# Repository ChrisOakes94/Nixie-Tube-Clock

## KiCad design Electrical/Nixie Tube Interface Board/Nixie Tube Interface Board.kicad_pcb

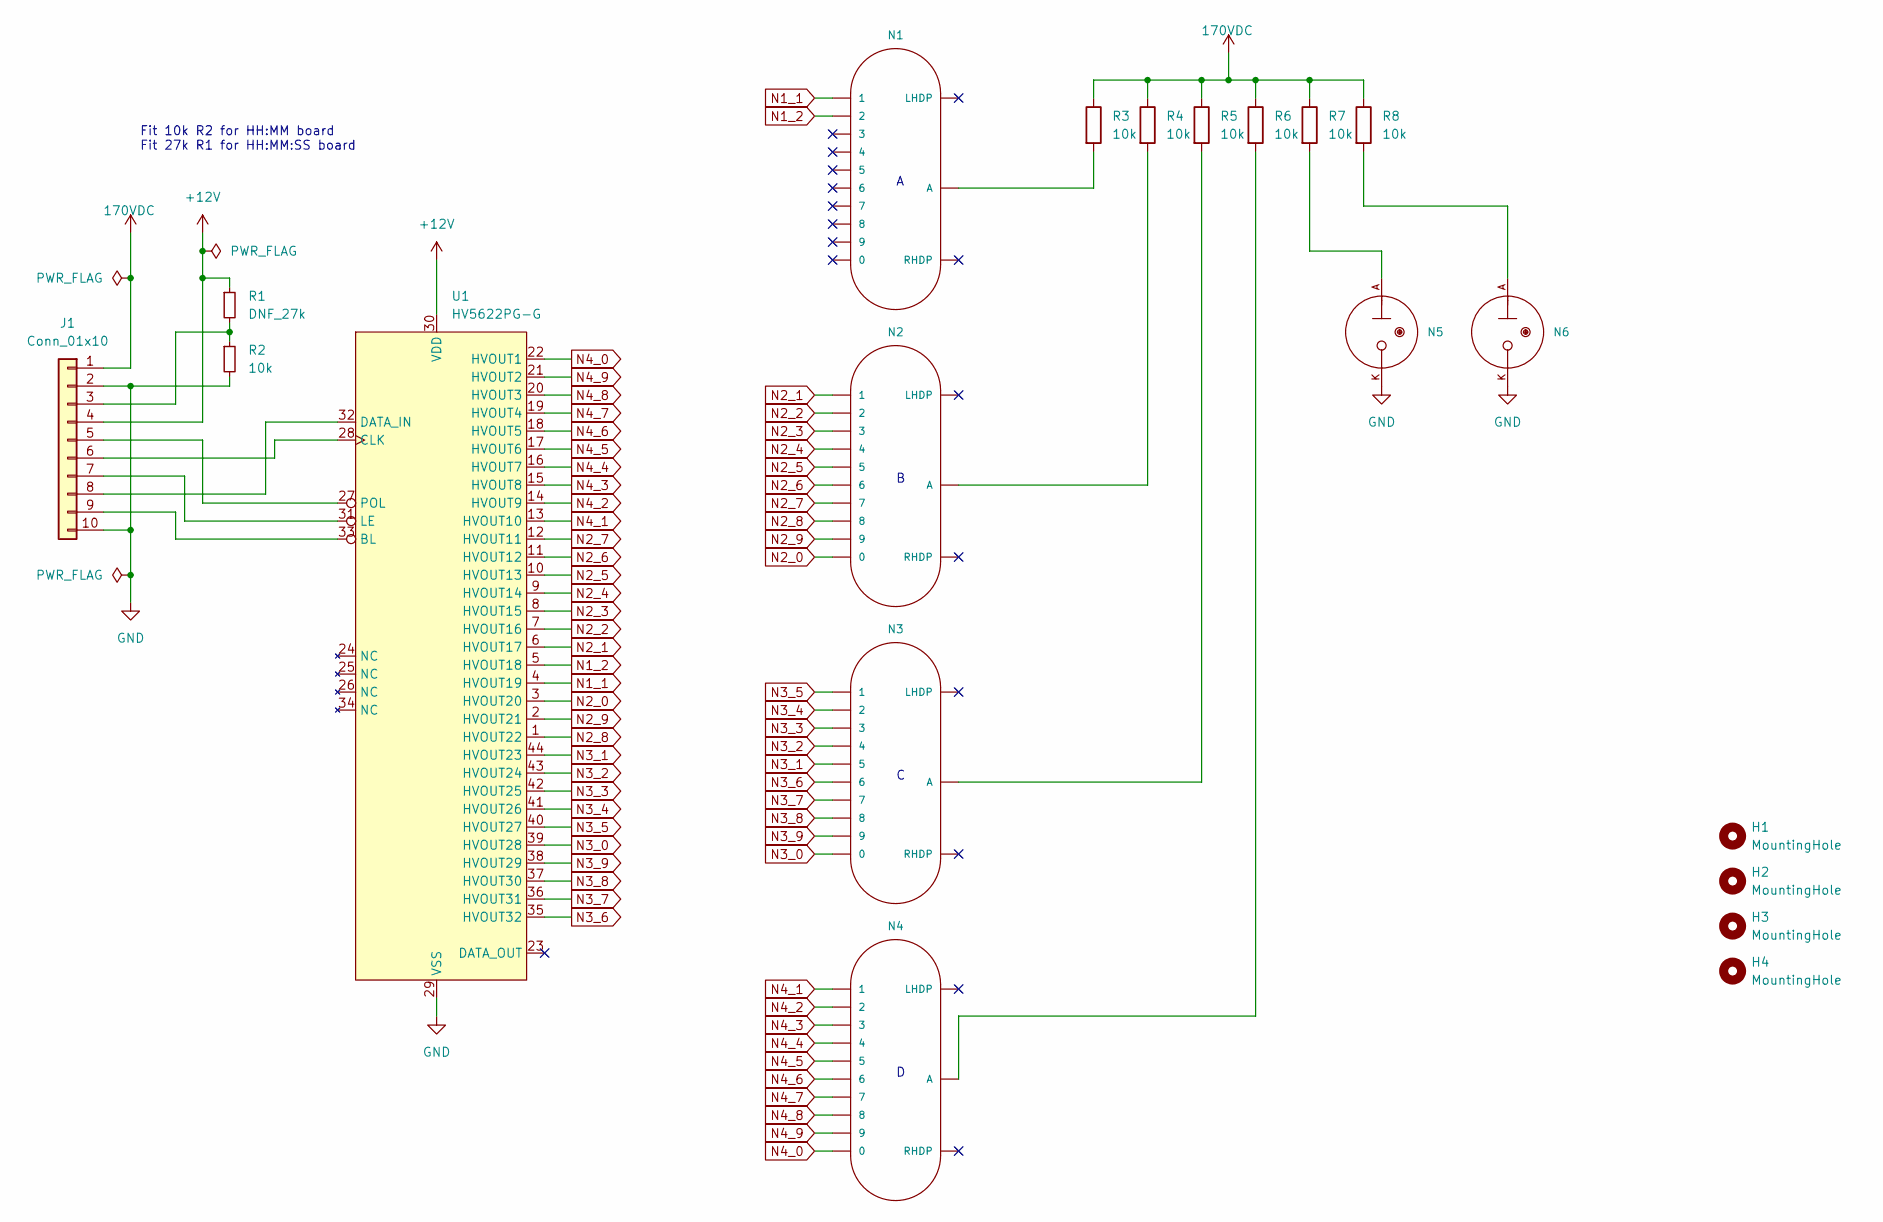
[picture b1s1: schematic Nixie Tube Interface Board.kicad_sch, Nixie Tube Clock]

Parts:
H1, H2, H3, H4: MountingHole; MountingHole_3.2mm_M3
J1: Conn_01x10; PinSocket_1x10_P2.54mm_Vertical
N1, N2, N3, N4: IN-14; nixies-us-IN-14
N5, N6: IN-3; nixies-us-IN-3
R1: DNF_27k; R_1206_3216Metric_Pad1.30x1.75mm_HandSolder
R2, R3, R4, R5, R6, R7, R8: 10k; R_1206_3216Metric_Pad1.30x1.75mm_HandSolder
U1: HV5622PG-G; LQFP-44_10x10mm_P0.8mm

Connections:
+12V: J1.4, R1.1, U1.30 (VDD)
+170VDC: J1.1, R3.1, R4.1, R5.1, R6.1, R7.1, R8.1
GND: J1.2, J1.10, N5.K, N6.K, R2.2, U1.29 (VSS)
N1_1: N1.1, U1.4 (HVOUT19)
N1_2: N1.2, U1.5 (HVOUT18)
N2_0: N2.0, U1.3 (HVOUT20)
N2_1: N2.1, U1.6 (HVOUT17)
N2_2: N2.2, U1.7 (HVOUT16)
N2_3: N2.3, U1.8 (HVOUT15)
N2_4: N2.4, U1.9 (HVOUT14)
N2_5: N2.5, U1.10 (HVOUT13)
N2_6: N2.6, U1.11 (HVOUT12)
N2_7: N2.7, U1.12 (HVOUT11)
N2_8: N2.8, U1.1 (HVOUT22)
N2_9: N2.9, U1.2 (HVOUT21)
N3_0: N3.0, U1.39 (HVOUT28)
N3_1: N3.5, U1.44 (HVOUT23)
N3_2: N3.4, U1.43 (HVOUT24)
N3_3: N3.3, U1.42 (HVOUT25)
N3_4: N3.2, U1.41 (HVOUT26)
N3_5: N3.1, U1.40 (HVOUT27)
N3_6: N3.6, U1.35 (HVOUT32)
N3_7: N3.7, U1.36 (HVOUT31)
N3_8: N3.8, U1.37 (HVOUT30)
N3_9: N3.9, U1.38 (HVOUT29)
N4_0: N4.0, U1.22 (HVOUT1)
N4_1: N4.1, U1.13 (HVOUT10)
N4_2: N4.2, U1.14 (HVOUT9)
N4_3: N4.3, U1.15 (HVOUT8)
N4_4: N4.4, U1.16 (HVOUT7)
N4_5: N4.5, U1.17 (HVOUT6)
N4_6: N4.6, U1.18 (HVOUT5)
N4_7: N4.7, U1.19 (HVOUT4)
N4_8: N4.8, U1.20 (HVOUT3)
N4_9: N4.9, U1.21 (HVOUT2)
unnamed: J1.3, R1.2, R2.1
unnamed: J1.5, U1.27 (POL)
unnamed: J1.6, U1.28 (CLK)
unnamed: J1.7, U1.31 (LE)
unnamed: J1.8, U1.32 (DATA_IN)
unnamed: J1.9, U1.33 (BL)
unnamed: N1.A, R3.2
unnamed: N2.A, R4.2
unnamed: N3.A, R5.2
unnamed: N4.A, R6.2
unnamed: N5.A, R7.2
unnamed: N6.A, R8.2

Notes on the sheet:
Fit 10k R2 for HH:MM board Fit 27k R1 for HH:MM:SS board

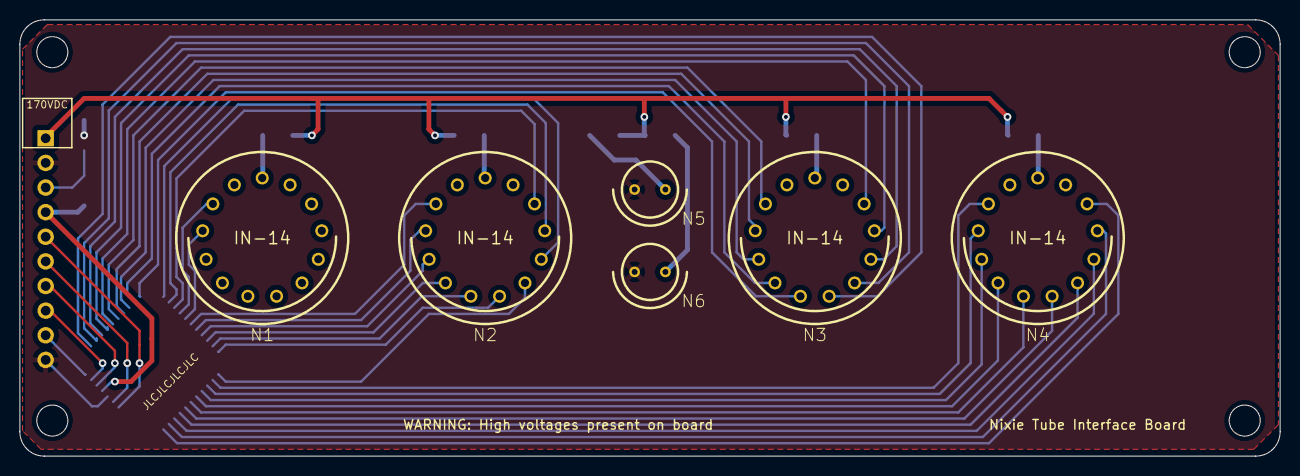
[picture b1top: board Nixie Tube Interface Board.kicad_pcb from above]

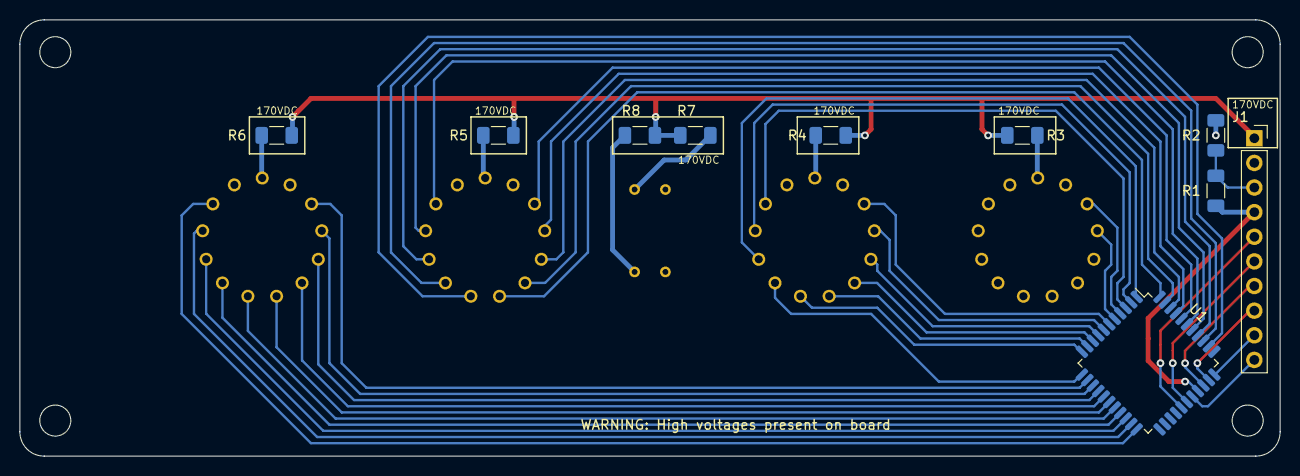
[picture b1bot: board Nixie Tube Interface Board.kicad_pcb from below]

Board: 2 copper layers, 130.0 x 45.0 mm, 20 parts (10 on the bottom side), 47 nets.

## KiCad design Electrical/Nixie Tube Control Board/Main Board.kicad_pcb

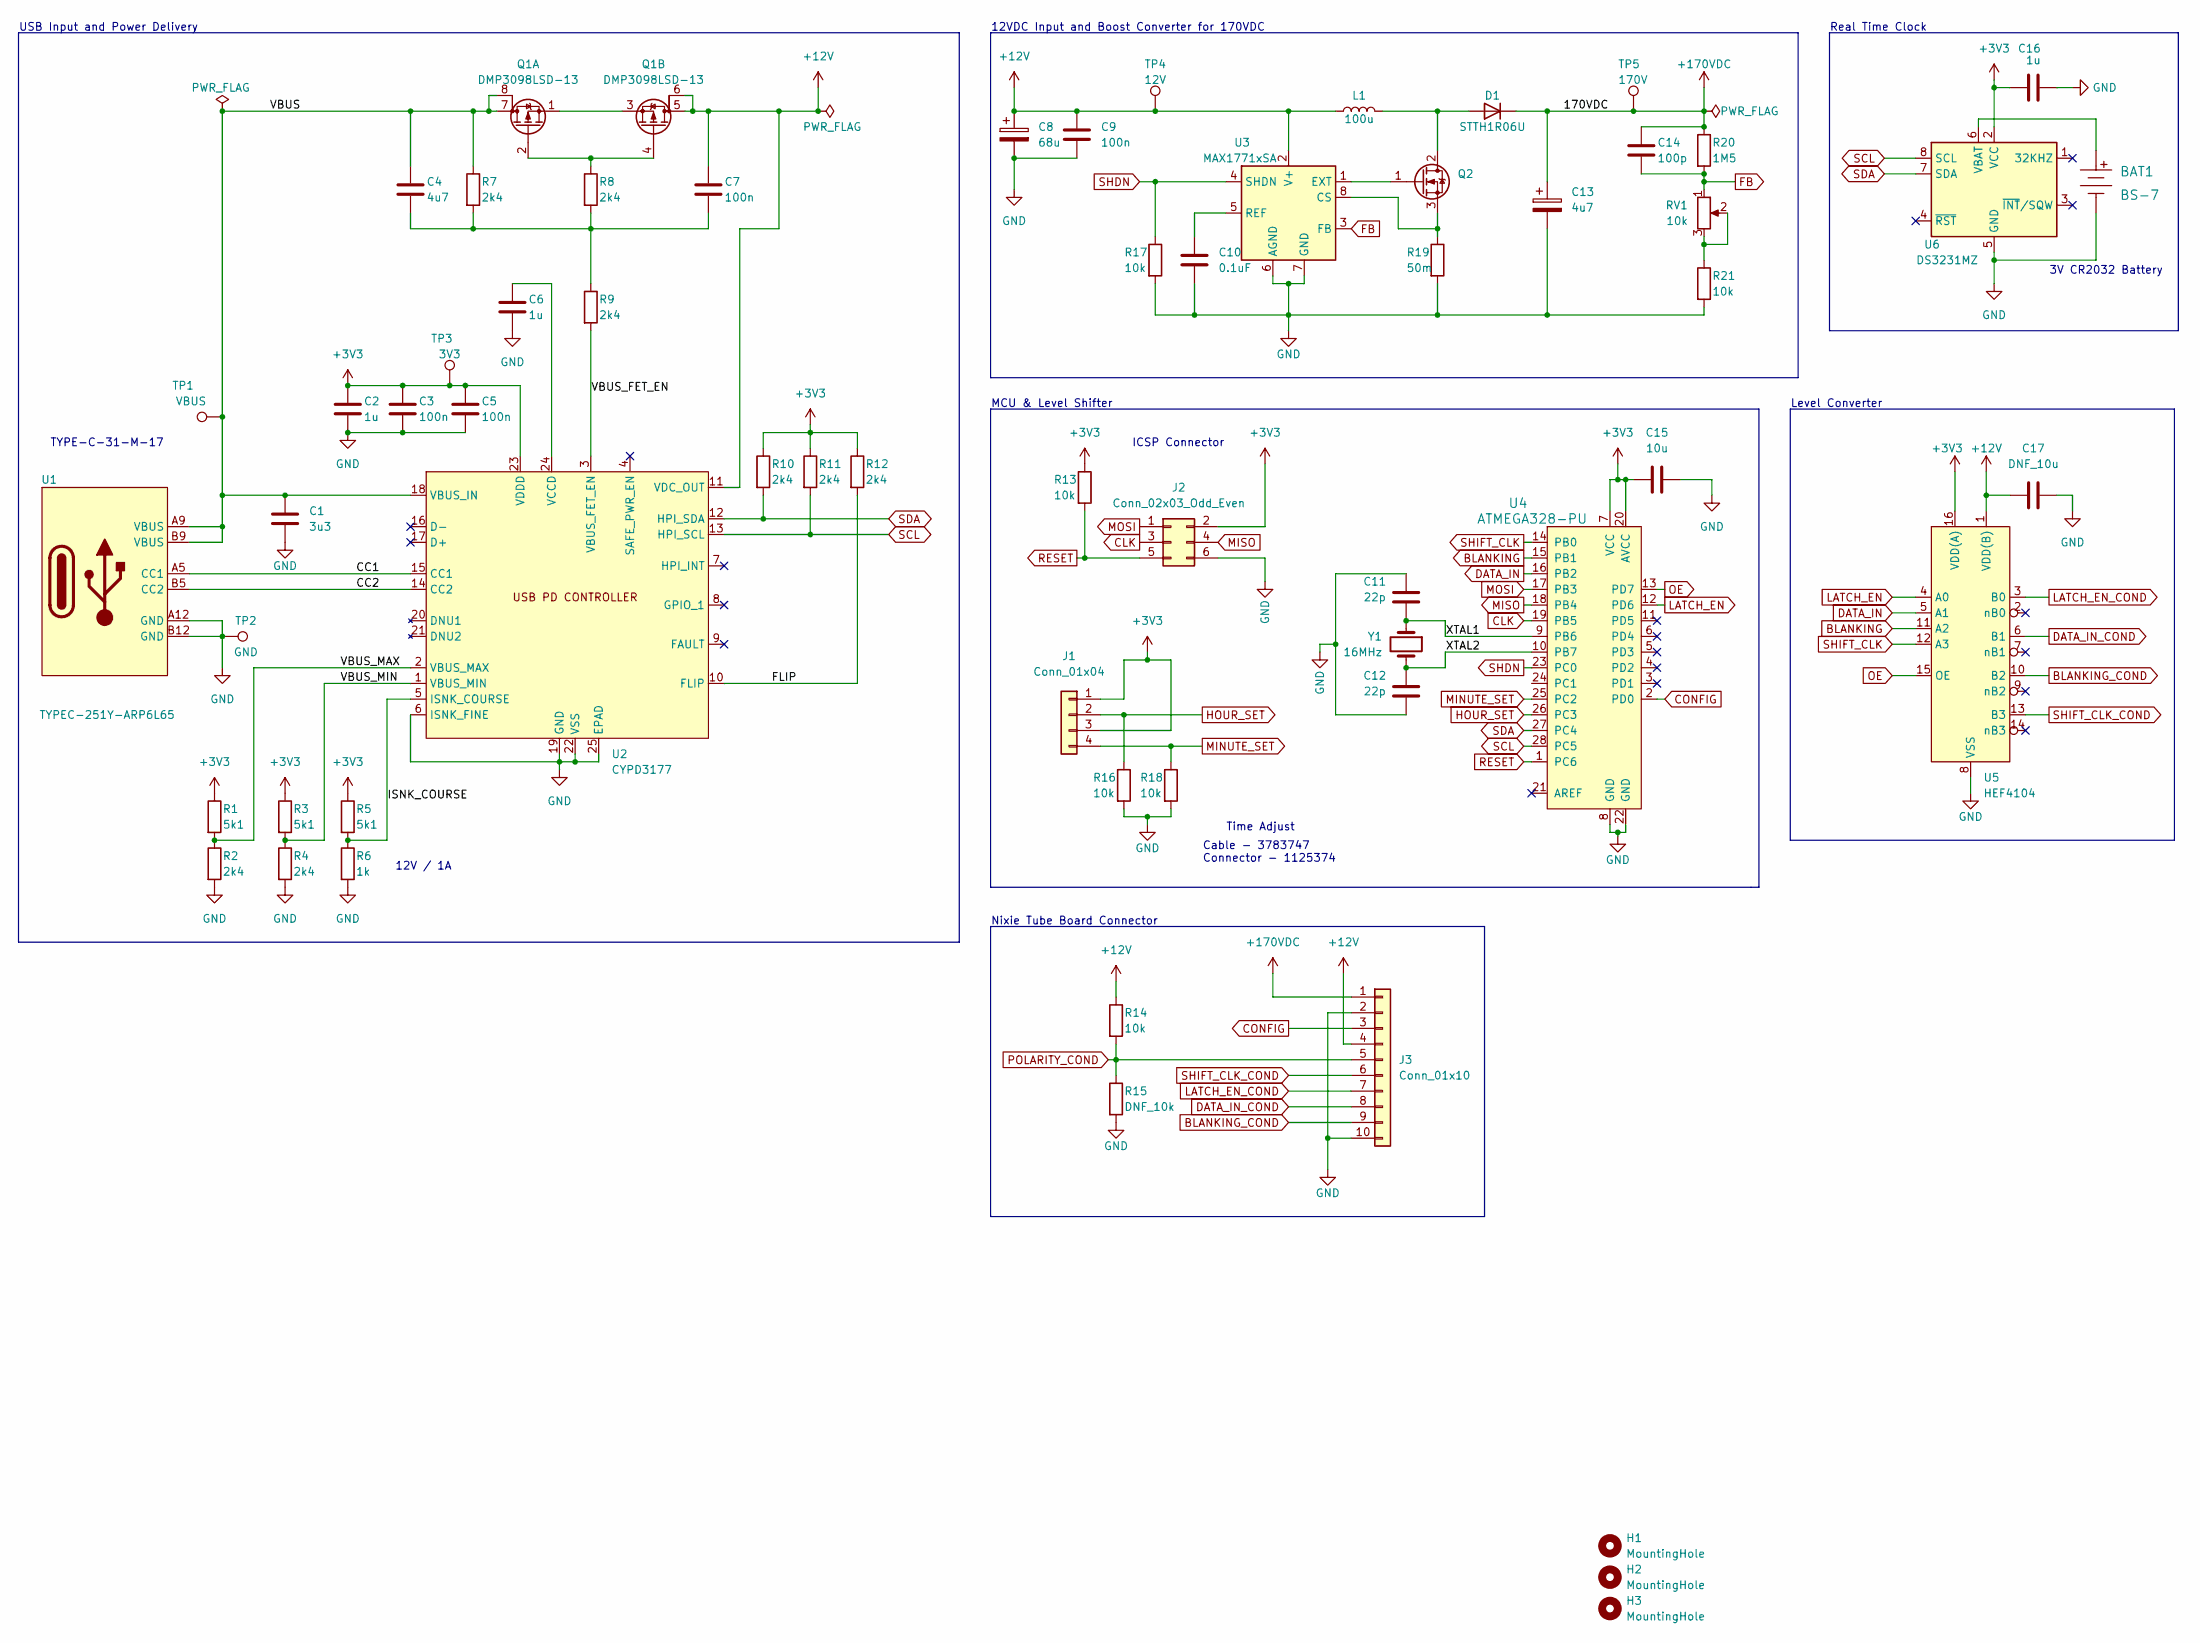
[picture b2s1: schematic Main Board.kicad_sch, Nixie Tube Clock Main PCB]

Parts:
BAT1: BS-7; Battery_Holder_Coin_2032_BS-7; MPN BS-7; Digi-Key_PN BS-7-ND
C1: 3u3; C_0805_2012Metric
C2, C6, C16: 1u; C_0805_2012Metric
C3, C5, C7, C9: 100n; C_0805_2012Metric
C4: 4u7; C_0805_2012Metric
C8: 68u; C_0805_2012Metric
C10: 0.1uF; C_0805_2012Metric
C11, C12: 22p; C_0805_2012Metric
C13: 4u7; CP_Elec_10x7.7; JLC P/N C2982253
C14: 100p; C_0805_2012Metric
C15: 10u; C_0805_2012Metric
C17: DNF_10u; C_0805_2012Metric
D1: STTH1R06U; D_SMB
H1, H2, H3: MountingHole; MountingHole_3.2mm_M3
J1: Conn_01x04; Molex 52361-0471
J2: Conn_02x03_Odd_Even; PinHeader_2x03_P2.54mm_Vertical
J3: Conn_01x10; PinHeader_1x10_P2.54mm_Vertical
L1: 100u; ETQP5M101YGK
Q1: DMP3098LSD-13; SOIC-8_3.9x4.9mm_P1.27mm
Q2: IPN70R600P7S; SOT-223-3
R1, R3, R5: 5k1; R_0805_2012Metric
R2, R4, R7, R8, R9, R10, R11, R12: 2k4; R_0805_2012Metric
R6: 1k; R_0805_2012Metric
R13, R14, R16, R17, R18, R21: 10k; R_0805_2012Metric
R15: DNF_10k; R_0805_2012Metric
R19: 50m; R_0805_2012Metric
R20: 1M5; R_1206_3216Metric
RV1: 10k; Potentiometer_Bourns_3214W_Vertical
TP1: VBUS; TestPoint_Pad_2.0x2.0mm
TP2: GND; TestPoint_Pad_2.0x2.0mm
TP3: 3V3; TestPoint_Pad_2.0x2.0mm
TP4: 12V; TestPoint_Pad_2.0x2.0mm
TP5: 170V; TestPoint_Pad_2.0x2.0mm
U1: TYPEC-251Y-ARP6L65
U2: CYPD3177; QFN-24-1EP_4x4mm_P0.5mm_EP2.6x2.6mm
U3: MAX1771xSA; SO-8_3.9x4.9mm_P1.27mm
U4: ATMEGA328-PU; QFP80P900X900X120-32N; MPN ATMEGA328-PU; Digi-Key_PN ATMEGA328-PU-ND
U5: HEF4104; SO-16_3.9x9.9mm_P1.27mm
U6: DS3231MZ; SOIC-8_3.9x4.9mm_P1.27mm
Y1: 16MHz; Crystal_HC49-U_Vertical

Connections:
+3V3: C2.1, C3.1, C5.1, C15.1, C16.1, J1.1, J1.3, J2.2, R1.1, R3.1, R5.1, R10.1, R11.1, R12.1, R13.1, TP3.1, U2.23 (VDDD), U4.7 (VCC), U4.20 (AVCC), U5.16 (VDD(A)), U6.2 (VCC)
+12V: C7.1, C8.1, C9.2, C17.1, J3.4, L1.1, Q1.5 (D), Q1.6 (G), R14.1, TP4.1, U2.11 (VDC_OUT), U3.2 (V+), U5.1 (VDD(B))
+170VDC: C13.1, C14.1, D1.1 (K), J3.1, R20.1, TP5.1
/CC1: U1.A5 (CC1), U2.15 (CC1)
/CC2: U1.B5 (CC2), U2.14 (CC2)
/FLIP: R12.2, U2.10 (FLIP)
/ISNK_COURSE: R5.2, R6.1, U2.5 (ISNK_COURSE)
/VBUS: C1.1, C4.1, Q1.7 (D), Q1.8 (G), R7.1, TP1.1, U1.A9 (VBUS), U1.B9 (VBUS), U2.18 (VBUS_IN)
/VBUS_FET_EN: R9.2, U2.3 (VBUS_FET_EN)
/VBUS_MAX: R1.2, R2.1, U2.2 (VBUS_MAX)
/VBUS_MIN: R3.2, R4.1, U2.1 (VBUS_MIN)
/XTAL1: C11.2, U4.9 (PB6), Y1.1
/XTAL2: C12.1, U4.10 (PB7), Y1.2
BLANKING: U4.15 (PB1), U5.11 (A2)
BLANKING_COND: J3.9, U5.10 (B2)
CLK: J2.3, U4.19 (PB5)
CONFIG: J3.3, U4.2 (PD0)
DATA_IN: U4.16 (PB2), U5.5 (A1)
DATA_IN_COND: J3.8, U5.6 (B1)
FB: C14.2, R20.2, RV1.1, U3.3 (FB)
GND: BAT1.Neg, C1.2, C2.2, C3.2, C5.2, C6.2, C8.2, C9.1, C10.2, C11.1, C12.2, C13.2, C15.2, C16.2, C17.2, J2.6, J3.2, J3.10, R2.2, R4.2, R6.2, R15.2, R16.2, R17.2, R18.2, R19.2, R21.2, TP2.1, U1.A12 (GND), U1.B12 (GND), U2.6 (ISNK_FINE), U2.19 (GND), U2.22 (VSS), U2.25 (EPAD), U3.6 (AGND), U3.7 (GND), U4.8 (GND), U4.22 (GND), U5.8 (VSS), U6.5 (GND)
HOUR_SET: J1.2, R16.1, U4.26 (PC3)
LATCH_EN: U4.12 (PD6), U5.4 (A0)
LATCH_EN_COND: J3.7, U5.3 (B0)
MINUTE_SET: J1.4, R18.1, U4.25 (PC2)
MISO: J2.4, U4.18 (PB4)
MOSI: J2.1, U4.17 (PB3)
unnamed: BAT1.Pos, U6.6 (VBAT)
unnamed: C4.2, C7.2, R7.2, R8.2, R9.1
unnamed: C6.1, U2.24 (VCCD)
unnamed: C10.1, U3.5 (REF)
unnamed: D1.2 (A), L1.2, Q2.2 (D)
unnamed: Q1.1 (S), Q1.3 (S)
unnamed: Q1.2 (G), Q1.4 (G), R8.1
unnamed: Q2.1 (G), U3.1 (EXT)
unnamed: Q2.3 (S), R19.1, U3.8 (CS)
unnamed: R21.1, RV1.2, RV1.3
OE: U4.13 (PD7), U5.15 (OE)
POLARITY_COND: J3.5, R14.2, R15.1
RESET: J2.5, R13.2, U4.1 (PC6)
SCL: R11.2, U2.13 (HPI_SCL), U4.28 (PC5), U6.8 (SCL)
SDA: R10.2, U2.12 (HPI_SDA), U4.27 (PC4), U6.7 (SDA)
SHDN: R17.1, U3.4 (SHDN), U4.23 (PC0)
SHIFT_CLK: U4.14 (PB0), U5.12 (A3)
SHIFT_CLK_COND: J3.6, U5.13 (B3)

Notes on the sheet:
Level Converter
Real Time Clock
MCU & Level Shifter
Time Adjust
12VDC Input and Boost Converter for 170VDC
TYPE-C-31-M-17
ICSP Connector
Cable - 3783747 Connector - 1125374
3V CR2032 Battery
USB Input and Power Delivery
12V / 1A
Nixie Tube Board Connector

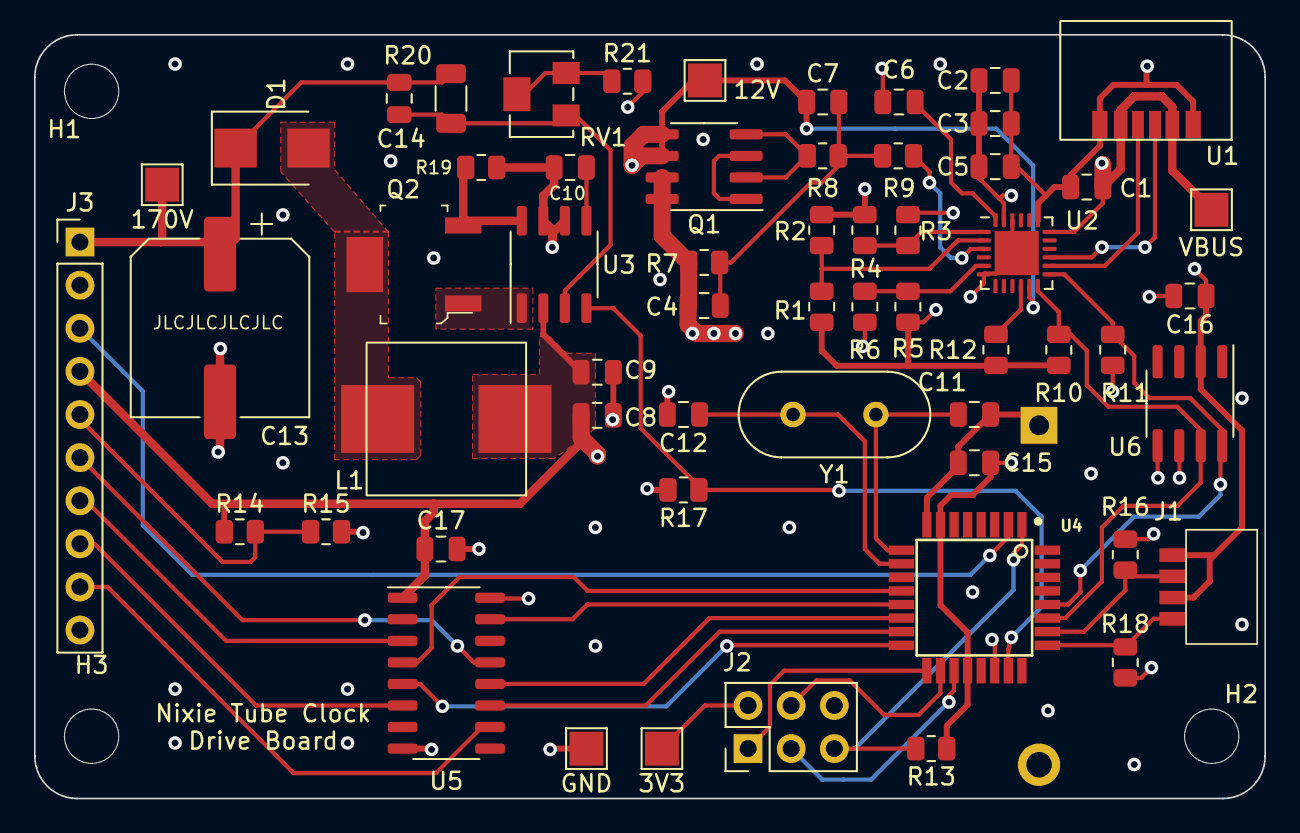
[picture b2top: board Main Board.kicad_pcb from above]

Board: 4 copper layers, 72.5 x 45.0 mm, 62 parts (1 on the bottom side), 45 nets.
